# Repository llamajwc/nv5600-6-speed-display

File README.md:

# nv5600-6-speed-display
PCB and oled display to show what gear postition for a NV5600 dodge ram diesel manual transmission.
1 x Display Waveshare 1.28inch round display https://www.amazon.com/Waveshare-1-28inch-LCD-Module-Resolution/dp/B08V5538C6
  I suggest this one, because the cheaper ones require more coding changes that can be frustrating. With this and the onboard GC9A01 driver, theirs more documentation and easir to understand the wiring.
    Display to arduino connections
D13 = SCK
D11 = MOSI
D10 = CS
D9 = DC
D8 = RST
BL = VCC (or D6 PWM if you want dimming)

8 x 10k resisters - pullup
8 x ah3503 hall effect sensors 
Arduino Nano 
magnets

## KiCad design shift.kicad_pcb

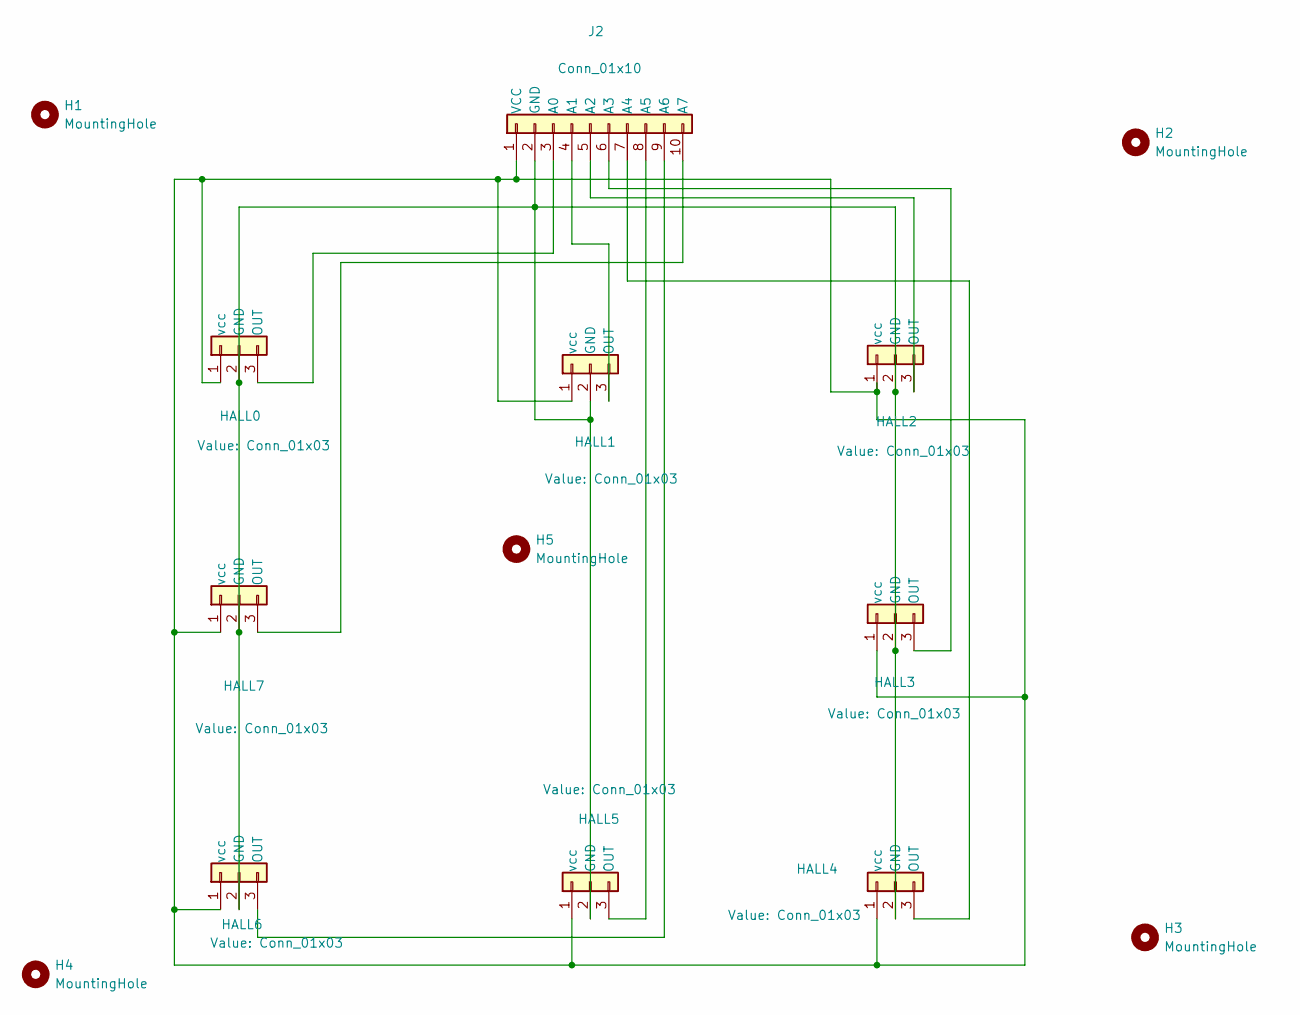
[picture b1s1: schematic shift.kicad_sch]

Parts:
H1, H2, H3, H4: MountingHole; MountingHole_6mm
H5: MountingHole; ToolingHole_1.152mm
HALL0, HALL1, HALL2, HALL3, HALL4, HALL5, HALL6, HALL7: Conn_01x03; PinHeader_1x03_P2.54mm_Vertical
J2: Conn_01x10; PinHeader_1x10_P2.54mm_Vertical

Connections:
unnamed: HALL0.2 (GND), HALL1.2 (GND), HALL2.2 (GND), HALL3.2 (GND), HALL4.2 (GND), HALL5.2 (GND), HALL6.2 (GND), HALL7.2 (GND), J2.2 (GND)
unnamed: HALL0.3 (OUT), J2.3 (A0)
unnamed: HALL0.1 (vcc), HALL1.1 (vcc), HALL2.1 (vcc), HALL3.1 (vcc), HALL4.1 (vcc), HALL5.1 (vcc), HALL6.1 (vcc), HALL7.1 (vcc), J2.1 (VCC)
unnamed: HALL1.3 (OUT), J2.4 (A1)
unnamed: HALL2.3 (OUT), J2.5 (A2)
unnamed: HALL3.3 (OUT), J2.6 (A3)
unnamed: HALL4.3 (OUT), J2.7 (A4)
unnamed: HALL5.3 (OUT), J2.8 (A5)
unnamed: HALL6.3 (OUT), J2.9 (A6)
unnamed: HALL7.3 (OUT), J2.10 (A7)

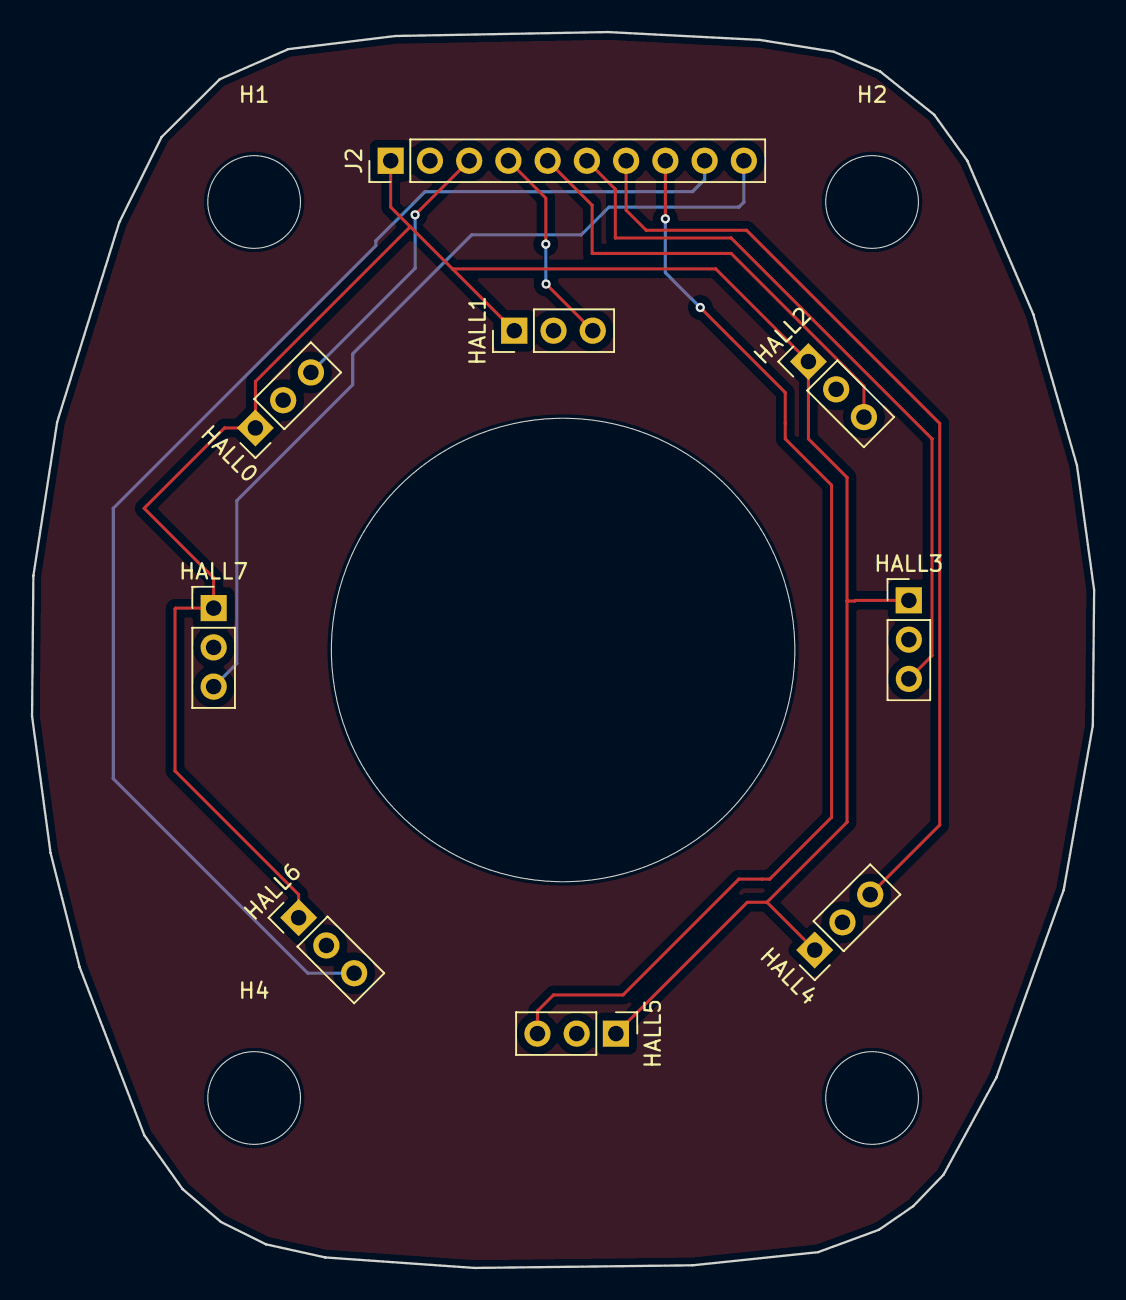
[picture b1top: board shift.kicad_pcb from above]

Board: 2 copper layers, 68.8 x 80.0 mm, 14 parts (0 on the bottom side), 10 nets.

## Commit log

2026-01-31 Add files via upload
    These are the Gerber files ready to upload to PCBWAY, or where ever for production.
    Note: this is my first one, the hall effect sensors need pulldown resistors, that i should have added to the board, but.. eh.
2026-01-31 Add files via upload
    Kicad schematic and pcb layouts,
